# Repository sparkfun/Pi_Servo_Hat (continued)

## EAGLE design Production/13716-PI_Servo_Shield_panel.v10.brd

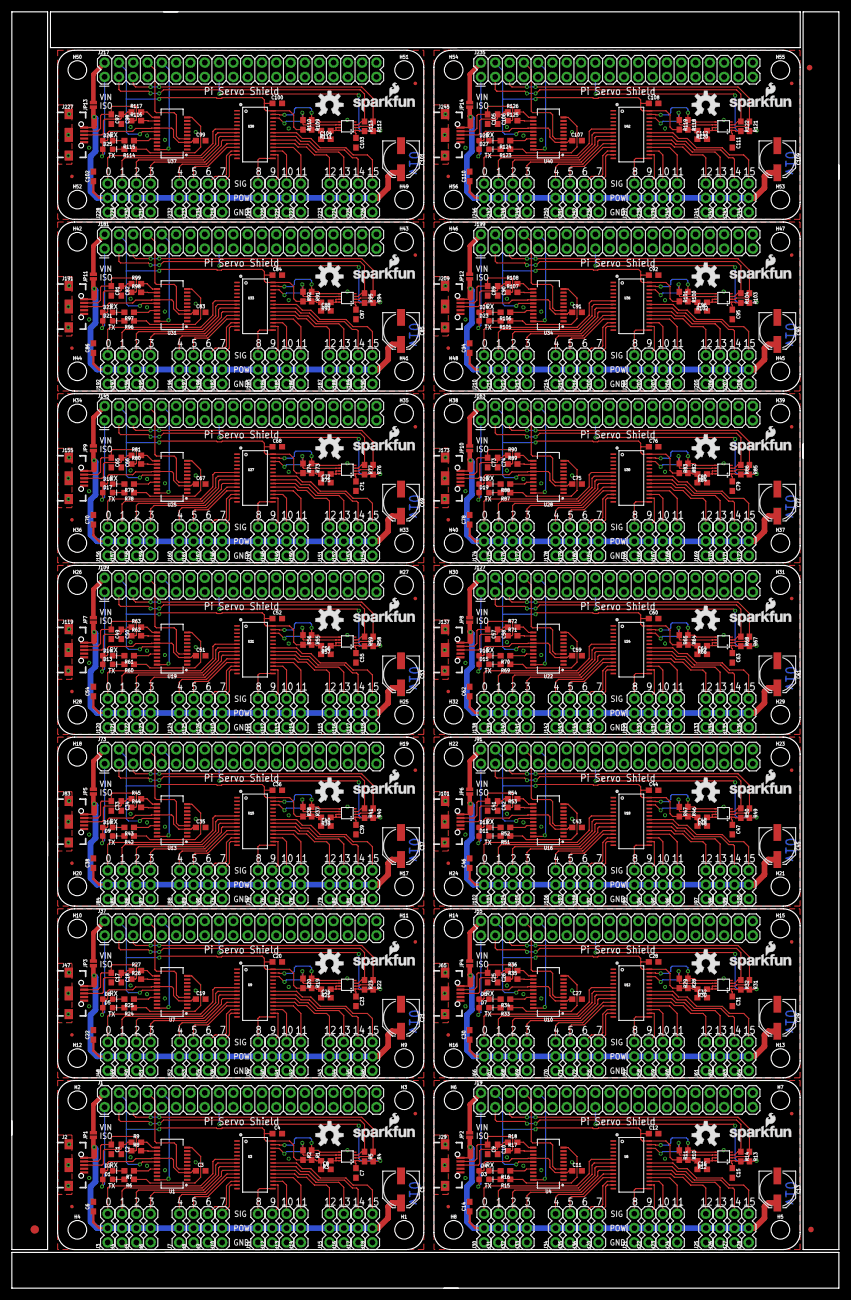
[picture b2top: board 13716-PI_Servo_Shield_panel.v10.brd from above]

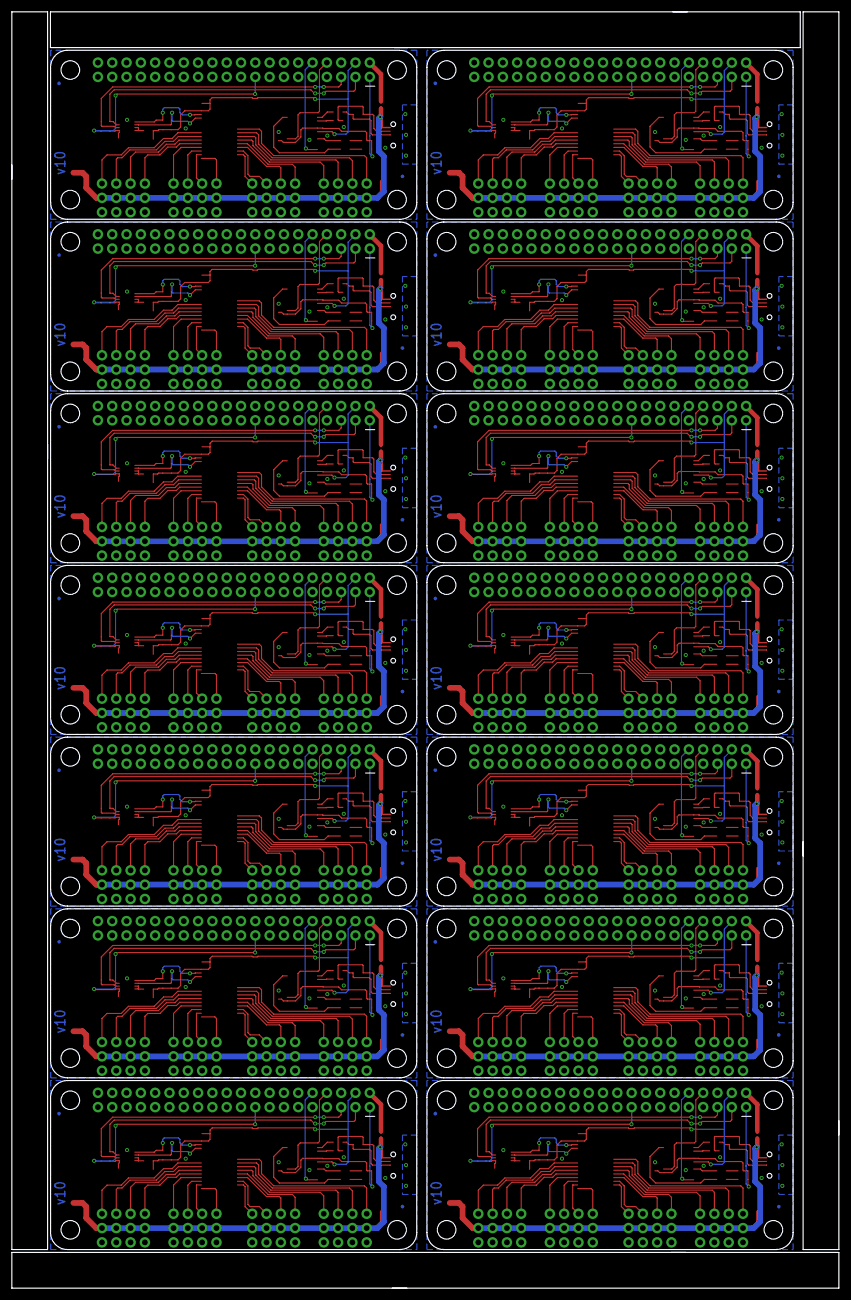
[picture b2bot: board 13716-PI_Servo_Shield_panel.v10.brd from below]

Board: 2 copper layers, 146.8 x 226.6 mm, 717 parts (28 on the bottom side), 532 nets.

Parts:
C1, C2, C9, C10, C17, C18, C25, C26, C33, C34, C41, C42, C49, C50, C57, C58, C65, C66, C73, C74, C81, C82, C89, C90, C97, C98, C105, C106: 47pF; 0603
C3, C4, C6, C7, C8, C11, C12, C14, C15, C16, C19, C20, C22, C23, C24, C27, C28, C30, C31, C32, C35, C36, C38, C39, C40, C43, C44, C46, C47, C48, C51, C52, C54, C55, C56, C59, C60, C62, C63, C64, C67, C68, C70, C71, C72, C75, C76, C78, C79, C80, C83, C84, C86, C87, C88, C91, C92, C94, C95, C96, C99, C100, C102, C103, C104, C107, C108, C110, C111, C112: 0.1uF; 0603
C5, C13, C21, C29, C37, C45, C53, C61, C69, C77, C85, C93, C101, C109: 100uF; PANASONIC_D
D1, D3, D5, D7, D9, D11, D13, D15, D17, D19, D21, D23, D25, D27: GREEN; LED-0603
D2, D4, D6, D8, D10, D12, D14, D16, D18, D20, D22, D24, D26, D28: Yellow; LED-0603
E$1: FIDUCIAL-1.5X3
E$7, E$8: FIDUCIAL-1X2
FD1, FD2, FD3, FD4, FD5, FD6, FD7, FD8, FD9, FD10, FD11, FD12, FD13, FD14, FD15, FD16, FD17, FD18, FD19, FD20, FD21, FD22, FD23, FD24, FD25, FD26, FD27, FD28, FD29, FD30, FD31, FD32, FD33, FD34, FD35, FD36, FD37, FD38, FD39, FD40, FD41, FD42, FD43, FD44, FD45, FD46, FD47, FD48, FD49, FD50, FD51, FD52, FD53, FD54, FD55, FD56: FIDUCIALUFIDUCIAL; FIDUCIAL-MICRO
H1, H2, H3, H4, H5, H6, H7, H8, H9, H10, H11, H12, H13, H14, H15, H16, H17, H18, H19, H20, H21, H22, H23, H24, H25, H26, H27, H28, H29, H30, H31, H32, H33, H34, H35, H36, H37, H38, H39, H40, H41, H42, H43, H44, H45, H46, H47, H48, H49, H50, H51, H52, H53, H54, H55, H56: STAND-OFF
J1, J19, J37, J55, J73, J91, J109, J127, J145, J163, J181, J199, J217, J235: RASPBERRYPI-40-PIN-GPIO_PTH_NO_SHROUD; 2X20
J2, J29, J47, J65, J83, J101, J119, J137, J155, J173, J191, J209, J227, J245: USB-B-MICRO-SMD
J3, J4, J5, J6, J7, J8, J9, J10, J11, J12, J13, J14, J15, J16, J17, J18, J20, J21, J22, J23, J24, J25, J26, J27, J28, J30, J31, J32, J33, J34, J35, J36, J38, J39, J40, J41, J42, J43, J44, J45, J46, J48, J49, J50, J51, J52, J53, J54, J56, J57, J58, J59, J60, J61, J62, J63, J64, J66, J67, J68, J69, J70, J71, J72, J74, J75, J76, J77, J78, J79, J80, J81, J82, J84, J85, J86, J87, J88, J89, J90, J92, J93, J94, J95, J96, J97, J98, J99, J100, J102, J103, J104, J105, J106, J107, J108, J110, J111, J112, J113, J114, J115, J116, J117, J118, J120, J121, J122, J123, J124, J125, J126, J128, J129, J130, J131, J132, J133, J134, J135, J136, J138, J139, J140, J141, J142, J143, J144, J146, J147, J148, J149, J150, J151, J152, J153, J154, J156, J157, J158, J159, J160, J161, J162, J164, J165, J166, J167, J168, J169, J170, J171, J172, J174, J175, J176, J177, J178, J179, J180, J182, J183, J184, J185, J186, J187, J188, J189, J190, J192, J193, J194, J195, J196, J197, J198, J200, J201, J202, J203, J204, J205, J206, J207, J208, J210, J211, J212, J213, J214, J215, J216, J218, J219, J220, J221, J222, J223, J224, J225, J226, J228, J229, J230, J231, J232, J233, J234, J236, J237, J238, J239, J240, J241, J242, J243, J244, J246, J247, J248, J249, J250, J251, J252: 1X03
JP1, JP2, JP3, JP4, JP5, JP6, JP7, JP8, JP9, JP10, JP11, JP12, JP13, JP14: JUMPER-SMT_2_NC_PASTE_NO-SILK; SMT-JUMPER_2_NC_PASTE_NO-SILK
LOGO1, LOGO3, LOGO5, LOGO7, LOGO9, LOGO11, LOGO13, LOGO15, LOGO17, LOGO19, LOGO21, LOGO23, LOGO25, LOGO27: SFE_LOGO_NAME_FLAME.1_INCH; SFE_LOGO_NAME_FLAME_.1
LOGO2, LOGO4, LOGO6, LOGO8, LOGO10, LOGO12, LOGO14, LOGO16, LOGO18, LOGO20, LOGO22, LOGO24, LOGO26, LOGO28: OSHW-LOGOM; OSHW-LOGO-M
R1, R2, R4, R5, R10, R11, R13, R14, R19, R20, R22, R23, R28, R29, R31, R32, R37, R38, R40, R41, R46, R47, R49, R50, R55, R56, R58, R59, R64, R65, R67, R68, R73, R74, R76, R77, R82, R83, R85, R86, R91, R92, R94, R95, R100, R101, R103, R104, R109, R110, R112, R113, R118, R119, R121, R122: 10k; 0603
R3, R12, R21, R30, R39, R48, R57, R66, R75, R84, R93, R102, R111, R120: 200k; 0603
R6, R7, R15, R16, R24, R25, R33, R34, R42, R43, R51, R52, R60, R61, R69, R70, R78, R79, R87, R88, R96, R97, R105, R106, R114, R115, R123, R124: 1k; 0603
R8, R9, R17, R18, R26, R27, R35, R36, R44, R45, R53, R54, R62, R63, R71, R72, R80, R81, R89, R90, R98, R99, R107, R108, R116, R117, R125, R126: 27; 0603
U1, U4, U7, U10, U13, U16, U19, U22, U25, U28, U31, U34, U37, U40: FT231XS; SSOP20_L
U2, U5, U8, U11, U14, U17, U20, U23, U26, U29, U32, U35, U38, U41: PCA9306; PSOP-8
U3, U6, U9, U12, U15, U18, U21, U24, U27, U30, U33, U36, U39, U42: PCA9685; TSSOP-28_4MM

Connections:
3.3VA: C3.1, D1.A, D2.A, J1.1, U1.3, U1.14
3.3VA1: C11.1, D3.A, D4.A, J19.1, U4.3, U4.14
3.3VA2: C19.1, D5.A, D6.A, J37.1, U7.3, U7.14
3.3VA3: C27.1, D7.A, D8.A, J55.1, U10.3, U10.14
3.3VA4: C35.1, D9.A, D10.A, J73.1, U13.3, U13.14
3.3VA5: C43.1, D11.A, D12.A, J91.1, U16.3, U16.14
3.3VA6: C51.1, D13.A, D14.A, J109.1, U19.3, U19.14
3.3VA7: C59.1, D15.A, D16.A, J127.1, U22.3, U22.14
3.3VA8: C67.1, D17.A, D18.A, J145.1, U25.3, U25.14
3.3VA9: C75.1, D19.A, D20.A, J163.1, U28.3, U28.14
3.3VA10: C83.1, D21.A, D22.A, J181.1, U31.3, U31.14
3.3VA11: C91.1, D23.A, D24.A, J199.1, U34.3, U34.14
3.3VA12: C99.1, D25.A, D26.A, J217.1, U37.3, U37.14
3.3VA13: C107.1, D27.A, D28.A, J235.1, U40.3, U40.14
3.3VB: C7.1, J1.17, R4.2, R5.2, U2.1
3.3VB1: C15.1, J19.17, R13.2, R14.2, U5.1
3.3VB2: C23.1, J37.17, R22.2, R23.2, U8.1
3.3VB3: C31.1, J55.17, R31.2, R32.2, U11.1
3.3VB4: C39.1, J73.17, R40.2, R41.2, U14.1
3.3VB5: C47.1, J91.17, R49.2, R50.2, U17.1
3.3VB6: C55.1, J109.17, R58.2, R59.2, U20.1
3.3VB7: C63.1, J127.17, R67.2, R68.2, U23.1
3.3VB8: C71.1, J145.17, R76.2, R77.2, U26.1
3.3VB9: C79.1, J163.17, R85.2, R86.2, U29.1
3.3VB10: C87.1, J181.17, R94.2, R95.2, U32.1
3.3VB11: C95.1, J199.17, R103.2, R104.2, U35.1
3.3VB12: C103.1, J217.17, R112.2, R113.2, U38.1
3.3VB13: C111.1, J235.17, R121.2, R122.2, U41.1
5VA: J1.2, JP1.2
5VA1: J19.2, JP2.2
5VA2: J37.2, JP3.2
5VA3: J55.2, JP4.2
5VA4: J73.2, JP5.2
5VA5: J91.2, JP6.2
5VA6: J109.2, JP7.2
5VA7: J127.2, JP8.2
5VA8: J145.2, JP9.2
5VA9: J163.2, JP10.2
5VA10: J181.2, JP11.2
5VA11: J199.2, JP12.2
5VA12: J217.2, JP13.2
5VA13: J235.2, JP14.2
5VB: C4.1, C8.1, J1.4, R1.2, R2.2, R3.2, U1.15, U3.28
5VB1: C12.1, C16.1, J19.4, R10.2, R11.2, R12.2, U4.15, U6.28
5VB2: C20.1, C24.1, J37.4, R19.2, R20.2, R21.2, U7.15, U9.28
5VB3: C28.1, C32.1, J55.4, R28.2, R29.2, R30.2, U10.15, U12.28
5VB4: C36.1, C40.1, J73.4, R37.2, R38.2, R39.2, U13.15, U15.28
5VB5: C44.1, C48.1, J91.4, R46.2, R47.2, R48.2, U16.15, U18.28
5VB6: C52.1, C56.1, J109.4, R55.2, R56.2, R57.2, U19.15, U21.28
5VB7: C60.1, C64.1, J127.4, R64.2, R65.2, R66.2, U22.15, U24.28
5VB8: C68.1, C72.1, J145.4, R73.2, R74.2, R75.2, U25.15, U27.28
5VB9: C76.1, C80.1, J163.4, R82.2, R83.2, R84.2, U28.15, U30.28
5VB10: C84.1, C88.1, J181.4, R91.2, R92.2, R93.2, U31.15, U33.28
5VB11: C92.1, C96.1, J199.4, R100.2, R101.2, R102.2, U34.15, U36.28
5VB12: C100.1, C104.1, J217.4, R109.2, R110.2, R111.2, U37.15, U39.28
5VB13: C108.1, C112.1, J235.4, R118.2, R119.2, R120.2, U40.15, U42.28
CH0: J3.3, U3.6
CH1: J4.3, U3.7
CH2: J5.3, U3.8
CH3: J6.3, U3.9
CH4: J7.3, U3.10
CH5: J8.3, U3.11
CH6: J9.3, U3.12
CH7: J10.3, U3.13
CH8: J11.3, U3.15
CH9: J12.3, U3.16
CH10: J13.3, U3.17
CH11: J14.3, U3.18
CH12: J15.3, U3.19
CH13: J16.3, U3.20
CH14: J17.3, U3.21
CH15: J18.3, U3.22
CH16: J28.3, U6.22
CH17: J27.3, U6.21
CH18: J26.3, U6.20
CH19: J25.3, U6.19
CH20: J24.3, U6.18
CH21: J23.3, U6.17
CH22: J22.3, U6.16
CH23: J21.3, U6.15
CH24: J36.3, U6.12
CH25: J35.3, U6.11
CH26: J34.3, U6.10
CH27: J33.3, U6.9
CH28: J32.3, U6.8
CH29: J31.3, U6.7
CH30: J30.3, U6.6
CH31: J20.3, U6.13
CH32: J46.3, U9.22
CH33: J45.3, U9.21
CH34: J44.3, U9.20
CH35: J43.3, U9.19
CH36: J42.3, U9.18
CH37: J41.3, U9.17
CH38: J40.3, U9.16
CH39: J39.3, U9.15
CH40: J54.3, U9.12
CH41: J53.3, U9.11
CH42: J52.3, U9.10
CH43: J51.3, U9.9
CH44: J50.3, U9.8
CH45: J49.3, U9.7
CH46: J48.3, U9.6
CH47: J38.3, U9.13
CH48: J64.3, U12.22
CH49: J63.3, U12.21
CH50: J62.3, U12.20
CH51: J61.3, U12.19
CH52: J60.3, U12.18
CH53: J59.3, U12.17
CH54: J58.3, U12.16
CH55: J57.3, U12.15
CH56: J72.3, U12.12
CH57: J71.3, U12.11
CH58: J70.3, U12.10
CH59: J69.3, U12.9
CH60: J68.3, U12.8
CH61: J67.3, U12.7
CH62: J66.3, U12.6
CH63: J56.3, U12.13
CH64: J82.3, U15.22
CH65: J81.3, U15.21
CH66: J80.3, U15.20
CH67: J79.3, U15.19
CH68: J78.3, U15.18
CH69: J77.3, U15.17
CH70: J76.3, U15.16
CH71: J75.3, U15.15
CH72: J90.3, U15.12
CH73: J89.3, U15.11
CH74: J88.3, U15.10
CH75: J87.3, U15.9
CH76: J86.3, U15.8
CH77: J85.3, U15.7
CH78: J84.3, U15.6
CH79: J74.3, U15.13
CH80: J100.3, U18.22
CH81: J99.3, U18.21
CH82: J98.3, U18.20
CH83: J97.3, U18.19
CH84: J96.3, U18.18
CH85: J95.3, U18.17
CH86: J94.3, U18.16
CH87: J93.3, U18.15
CH88: J108.3, U18.12
CH89: J107.3, U18.11
CH90: J106.3, U18.10
CH91: J105.3, U18.9
CH92: J104.3, U18.8
CH93: J103.3, U18.7
CH94: J102.3, U18.6
CH95: J92.3, U18.13
CH96: J118.3, U21.22
CH97: J117.3, U21.21
CH98: J116.3, U21.20
CH99: J115.3, U21.19
CH100: J114.3, U21.18
CH101: J113.3, U21.17
CH102: J112.3, U21.16
CH103: J111.3, U21.15
CH104: J126.3, U21.12
CH105: J125.3, U21.11
CH106: J124.3, U21.10
CH107: J123.3, U21.9
CH108: J122.3, U21.8
CH109: J121.3, U21.7
CH110: J120.3, U21.6
CH111: J110.3, U21.13
CH112: J136.3, U24.22
CH113: J135.3, U24.21
CH114: J134.3, U24.20
CH115: J133.3, U24.19
CH116: J132.3, U24.18
CH117: J131.3, U24.17
CH118: J130.3, U24.16
CH119: J129.3, U24.15
CH120: J144.3, U24.12
CH121: J143.3, U24.11
CH122: J142.3, U24.10
CH123: J141.3, U24.9
CH124: J140.3, U24.8
CH125: J139.3, U24.7
CH126: J138.3, U24.6
CH127: J128.3, U24.13
CH128: J154.3, U27.22
CH129: J153.3, U27.21
CH130: J152.3, U27.20
CH131: J151.3, U27.19
CH132: J150.3, U27.18
CH133: J149.3, U27.17
CH134: J148.3, U27.16
CH135: J147.3, U27.15
CH136: J162.3, U27.12
CH137: J161.3, U27.11
CH138: J160.3, U27.10
CH139: J159.3, U27.9
CH140: J158.3, U27.8
CH141: J157.3, U27.7
CH142: J156.3, U27.6
CH143: J146.3, U27.13
CH144: J172.3, U30.22
CH145: J171.3, U30.21
CH146: J170.3, U30.20
CH147: J169.3, U30.19
CH148: J168.3, U30.18
CH149: J167.3, U30.17
CH150: J166.3, U30.16
CH151: J165.3, U30.15
CH152: J180.3, U30.12
CH153: J179.3, U30.11
CH154: J178.3, U30.10
CH155: J177.3, U30.9
CH156: J176.3, U30.8
CH157: J175.3, U30.7
CH158: J174.3, U30.6
CH159: J164.3, U30.13
CH160: J190.3, U33.22
CH161: J189.3, U33.21
CH162: J188.3, U33.20
CH163: J187.3, U33.19
CH164: J186.3, U33.18
CH165: J185.3, U33.17
CH166: J184.3, U33.16
CH167: J183.3, U33.15
CH168: J198.3, U33.12
CH169: J197.3, U33.11
CH170: J196.3, U33.10
CH171: J195.3, U33.9
CH172: J194.3, U33.8
CH173: J193.3, U33.7
CH174: J192.3, U33.6
CH175: J182.3, U33.13
CH176: J208.3, U36.22
CH177: J207.3, U36.21
CH178: J206.3, U36.20
CH179: J205.3, U36.19
CH180: J204.3, U36.18
CH181: J203.3, U36.17
CH182: J202.3, U36.16
CH183: J201.3, U36.15
CH184: J216.3, U36.12
CH185: J215.3, U36.11
CH186: J214.3, U36.10
CH187: J213.3, U36.9
CH188: J212.3, U36.8
CH189: J211.3, U36.7
CH190: J210.3, U36.6
CH191: J200.3, U36.13
CH192: J226.3, U39.22
CH193: J225.3, U39.21
CH194: J224.3, U39.20
CH195: J223.3, U39.19
CH196: J222.3, U39.18
CH197: J221.3, U39.17
CH198: J220.3, U39.16
CH199: J219.3, U39.15
CH200: J234.3, U39.12
CH201: J233.3, U39.11
CH202: J232.3, U39.10
CH203: J231.3, U39.9
CH204: J230.3, U39.8
CH205: J229.3, U39.7
CH206: J228.3, U39.6
CH207: J218.3, U39.13
CH208: J244.3, U42.22
CH209: J243.3, U42.21
CH210: J242.3, U42.20
CH211: J241.3, U42.19
CH212: J240.3, U42.18
CH213: J239.3, U42.17
CH214: J238.3, U42.16
CH215: J237.3, U42.15
CH216: J252.3, U42.12
CH217: J251.3, U42.11
CH218: J250.3, U42.10
CH219: J249.3, U42.9
CH220: J248.3, U42.8
CH221: J247.3, U42.7
CH222: J246.3, U42.6
CH223: J236.3, U42.13
GND: C1.2, C2.2, C3.2, C4.2, C5.-, C6.2, C7.2, C8.2, J1.6, J1.9, J1.14, J1.20, J1.25, J1.30, J1.34, J1.39, J2.GND, J3.1, J4.1, J5.1, J6.1, J7.1, J8.1, J9.1, J10.1, J11.1, J12.1, J13.1, J14.1, J15.1, J16.1, J17.1, J18.1, U1.6, U1.16, U2.4, U3.14, U3.23, U3.25
GND1: C9.2, C10.2, C11.2, C12.2, C13.-, C14.2, C15.2, C16.2, J19.6, J19.9, J19.14, J19.20, J19.25, J19.30, J19.34, J19.39, J20.1, J21.1, J22.1, J23.1, J24.1, J25.1, J26.1, J27.1, J28.1, J29.GND, J30.1, J31.1, J32.1, J33.1, J34.1, J35.1, J36.1, U4.6, U4.16, U5.4, U6.14, U6.23, U6.25
GND2: C17.2, C18.2, C19.2, C20.2, C21.-, C22.2, C23.2, C24.2, J37.6, J37.9, J37.14, J37.20, J37.25, J37.30, J37.34, J37.39, J38.1, J39.1, J40.1, J41.1, J42.1, J43.1, J44.1, J45.1, J46.1, J47.GND, J48.1, J49.1, J50.1, J51.1, J52.1, J53.1, J54.1, U7.6, U7.16, U8.4, U9.14, U9.23, U9.25
GND3: C25.2, C26.2, C27.2, C28.2, C29.-, C30.2, C31.2, C32.2, J55.6, J55.9, J55.14, J55.20, J55.25, J55.30, J55.34, J55.39, J56.1, J57.1, J58.1, J59.1, J60.1, J61.1, J62.1, J63.1, J64.1, J65.GND, J66.1, J67.1, J68.1, J69.1, J70.1, J71.1, J72.1, U10.6, U10.16, U11.4, U12.14, U12.23, U12.25
GND4: C33.2, C34.2, C35.2, C36.2, C37.-, C38.2, C39.2, C40.2, J73.6, J73.9, J73.14, J73.20, J73.25, J73.30, J73.34, J73.39, J74.1, J75.1, J76.1, J77.1, J78.1, J79.1, J80.1, J81.1, J82.1, J83.GND, J84.1, J85.1, J86.1, J87.1, J88.1, J89.1, J90.1, U13.6, U13.16, U14.4, U15.14, U15.23, U15.25
GND5: C41.2, C42.2, C43.2, C44.2, C45.-, C46.2, C47.2, C48.2, J91.6, J91.9, J91.14, J91.20, J91.25, J91.30, J91.34, J91.39, J92.1, J93.1, J94.1, J95.1, J96.1, J97.1, J98.1, J99.1, J100.1, J101.GND, J102.1, J103.1, J104.1, J105.1, J106.1, J107.1, J108.1, U16.6, U16.16, U17.4, U18.14, U18.23, U18.25
GND6: C49.2, C50.2, C51.2, C52.2, C53.-, C54.2, C55.2, C56.2, J109.6, J109.9, J109.14, J109.20, J109.25, J109.30, J109.34, J109.39, J110.1, J111.1, J112.1, J113.1, J114.1, J115.1, J116.1, J117.1, J118.1, J119.GND, J120.1, J121.1, J122.1, J123.1, J124.1, J125.1, J126.1, U19.6, U19.16, U20.4, U21.14, U21.23, U21.25
GND7: C57.2, C58.2, C59.2, C60.2, C61.-, C62.2, C63.2, C64.2, J127.6, J127.9, J127.14, J127.20, J127.25, J127.30, J127.34, J127.39, J128.1, J129.1, J130.1, J131.1, J132.1, J133.1, J134.1, J135.1, J136.1, J137.GND, J138.1, J139.1, J140.1, J141.1, J142.1, J143.1, J144.1, U22.6, U22.16, U23.4, U24.14, U24.23, U24.25
GND8: C65.2, C66.2, C67.2, C68.2, C69.-, C70.2, C71.2, C72.2, J145.6, J145.9, J145.14, J145.20, J145.25, J145.30, J145.34, J145.39, J146.1, J147.1, J148.1, J149.1, J150.1, J151.1, J152.1, J153.1, J154.1, J155.GND, J156.1, J157.1, J158.1, J159.1, J160.1, J161.1, J162.1, U25.6, U25.16, U26.4, U27.14, U27.23, U27.25
GND9: C73.2, C74.2, C75.2, C76.2, C77.-, C78.2, C79.2, C80.2, J163.6, J163.9, J163.14, J163.20, J163.25, J163.30, J163.34, J163.39, J164.1, J165.1, J166.1, J167.1, J168.1, J169.1, J170.1, J171.1, J172.1, J173.GND, J174.1, J175.1, J176.1, J177.1, J178.1, J179.1, J180.1, U28.6, U28.16, U29.4, U30.14, U30.23, U30.25
GND10: C81.2, C82.2, C83.2, C84.2, C85.-, C86.2, C87.2, C88.2, J181.6, J181.9, J181.14, J181.20, J181.25, J181.30, J181.34, J181.39, J182.1, J183.1, J184.1, J185.1, J186.1, J187.1, J188.1, J189.1, J190.1, J191.GND, J192.1, J193.1, J194.1, J195.1, J196.1, J197.1, J198.1, U31.6, U31.16, U32.4, U33.14, U33.23, U33.25
GND11: C89.2, C90.2, C91.2, C92.2, C93.-, C94.2, C95.2, C96.2, J199.6, J199.9, J199.14, J199.20, J199.25, J199.30, J199.34, J199.39, J200.1, J201.1, J202.1, J203.1, J204.1, J205.1, J206.1, J207.1, J208.1, J209.GND, J210.1, J211.1, J212.1, J213.1, J214.1, J215.1, J216.1, U34.6, U34.16, U35.4, U36.14, U36.23, U36.25
GND12: C97.2, C98.2, C99.2, C100.2, C101.-, C102.2, C103.2, C104.2, J217.6, J217.9, J217.14, J217.20, J217.25, J217.30, J217.34, J217.39, J218.1, J219.1, J220.1, J221.1, J222.1, J223.1, J224.1, J225.1, J226.1, J227.GND, J228.1, J229.1, J230.1, J231.1, J232.1, J233.1, J234.1, U37.6, U37.16, U38.4, U39.14, U39.23, U39.25
GND13: C105.2, C106.2, C107.2, C108.2, C109.-, C110.2, C111.2, C112.2, J235.6, J235.9, J235.14, J235.20, J235.25, J235.30, J235.34, J235.39, J236.1, J237.1, J238.1, J239.1, J240.1, J241.1, J242.1, J243.1, J244.1, J245.GND, J246.1, J247.1, J248.1, J249.1, J250.1, J251.1, J252.1, U40.6, U40.16, U41.4, U42.14, U42.23, U42.25
LV_SCL: J1.5, R4.1, U2.2
LV_SCL1: J19.5, R13.1, U5.2
LV_SCL2: J37.5, R22.1, U8.2
LV_SCL3: J55.5, R31.1, U11.2
LV_SCL4: J73.5, R40.1, U14.2
LV_SCL5: J91.5, R49.1, U17.2
LV_SCL6: J109.5, R58.1, U20.2
LV_SCL7: J127.5, R67.1, U23.2
LV_SCL8: J145.5, R76.1, U26.2
LV_SCL9: J163.5, R85.1, U29.2
LV_SCL10: J181.5, R94.1, U32.2
LV_SCL11: J199.5, R103.1, U35.2
LV_SCL12: J217.5, R112.1, U38.2
LV_SCL13: J235.5, R121.1, U41.2
LV_SDA: J1.3, R5.1, U2.3
LV_SDA1: J19.3, R14.1, U5.3
LV_SDA2: J37.3, R23.1, U8.3
LV_SDA3: J55.3, R32.1, U11.3
LV_SDA4: J73.3, R41.1, U14.3
LV_SDA5: J91.3, R50.1, U17.3
LV_SDA6: J109.3, R59.1, U20.3
LV_SDA7: J127.3, R68.1, U23.3
LV_SDA8: J145.3, R77.1, U26.3
LV_SDA9: J163.3, R86.1, U29.3
LV_SDA10: J181.3, R95.1, U32.3
LV_SDA11: J199.3, R104.1, U35.3
LV_SDA12: J217.3, R113.1, U38.3
LV_SDA13: J235.3, R122.1, U41.3
unnamed: R3.1, U2.7, U2.8
unnamed: R8.2, U1.12
unnamed: R2.1, U2.6, U3.26
unnamed: R1.1, U2.5, U3.27
unnamed: D2.C, R7.2
unnamed: D1.C, R6.2
unnamed: R7.1, U1.17
unnamed: R6.1, U1.10
unnamed: R9.2, U1.11
unnamed: C2.1, J2.D+, R9.1
unnamed: C1.1, J2.D-, R8.1
unnamed: R12.1, U5.7, U5.8
unnamed: R11.1, U5.6, U6.26
unnamed: R10.1, U5.5, U6.27
unnamed: D4.C, R16.2
unnamed: D3.C, R15.2
unnamed: R16.1, U4.17
unnamed: R15.1, U4.10
unnamed: R17.2, U4.12
unnamed: R18.2, U4.11
unnamed: C10.1, J29.D+, R18.1
unnamed: C9.1, J29.D-, R17.1
unnamed: R21.1, U8.7, U8.8
unnamed: R20.1, U8.6, U9.26
unnamed: R19.1, U8.5, U9.27
unnamed: D6.C, R25.2
unnamed: D5.C, R24.2
unnamed: R25.1, U7.17
unnamed: R24.1, U7.10
unnamed: R26.2, U7.12
unnamed: R27.2, U7.11
unnamed: C18.1, J47.D+, R27.1
unnamed: C17.1, J47.D-, R26.1
unnamed: R30.1, U11.7, U11.8
unnamed: R29.1, U11.6, U12.26
unnamed: R28.1, U11.5, U12.27
unnamed: D8.C, R34.2
unnamed: D7.C, R33.2
unnamed: R34.1, U10.17
unnamed: R33.1, U10.10
unnamed: R35.2, U10.12
unnamed: R36.2, U10.11
unnamed: C26.1, J65.D+, R36.1
unnamed: C25.1, J65.D-, R35.1
unnamed: R39.1, U14.7, U14.8
unnamed: R38.1, U14.6, U15.26
unnamed: R37.1, U14.5, U15.27
unnamed: D10.C, R43.2
unnamed: D9.C, R42.2
unnamed: R43.1, U13.17
unnamed: R42.1, U13.10
unnamed: R44.2, U13.12
unnamed: R45.2, U13.11
unnamed: C34.1, J83.D+, R45.1
unnamed: C33.1, J83.D-, R44.1
unnamed: R48.1, U17.7, U17.8
unnamed: R47.1, U17.6, U18.26
unnamed: R46.1, U17.5, U18.27
unnamed: D12.C, R52.2
unnamed: D11.C, R51.2
unnamed: R52.1, U16.17
unnamed: R51.1, U16.10
unnamed: R53.2, U16.12
unnamed: R54.2, U16.11
unnamed: C42.1, J101.D+, R54.1
unnamed: C41.1, J101.D-, R53.1
unnamed: R57.1, U20.7, U20.8
unnamed: R56.1, U20.6, U21.26
unnamed: R55.1, U20.5, U21.27
unnamed: D14.C, R61.2
unnamed: D13.C, R60.2
unnamed: R61.1, U19.17
unnamed: R60.1, U19.10
unnamed: R62.2, U19.12
unnamed: R63.2, U19.11
unnamed: C50.1, J119.D+, R63.1
unnamed: C49.1, J119.D-, R62.1
unnamed: R66.1, U23.7, U23.8
unnamed: R65.1, U23.6, U24.26
unnamed: R64.1, U23.5, U24.27
unnamed: D16.C, R70.2
unnamed: D15.C, R69.2
unnamed: R70.1, U22.17
unnamed: R69.1, U22.10
unnamed: R71.2, U22.12
unnamed: R72.2, U22.11
unnamed: C58.1, J137.D+, R72.1
unnamed: C57.1, J137.D-, R71.1
unnamed: R75.1, U26.7, U26.8
unnamed: R74.1, U26.6, U27.26
unnamed: R73.1, U26.5, U27.27
unnamed: D18.C, R79.2
unnamed: D17.C, R78.2
unnamed: R79.1, U25.17
unnamed: R78.1, U25.10
unnamed: R80.2, U25.12
unnamed: R81.2, U25.11
unnamed: C66.1, J155.D+, R81.1
unnamed: C65.1, J155.D-, R80.1
unnamed: R84.1, U29.7, U29.8
unnamed: R83.1, U29.6, U30.26
unnamed: R82.1, U29.5, U30.27
unnamed: D20.C, R88.2
unnamed: D19.C, R87.2
unnamed: R88.1, U28.17
unnamed: R87.1, U28.10
unnamed: R89.2, U28.12
unnamed: R90.2, U28.11
unnamed: C74.1, J173.D+, R90.1
unnamed: C73.1, J173.D-, R89.1
unnamed: R93.1, U32.7, U32.8
unnamed: R92.1, U32.6, U33.26
unnamed: R91.1, U32.5, U33.27
unnamed: D22.C, R97.2
unnamed: D21.C, R96.2
unnamed: R97.1, U31.17
unnamed: R96.1, U31.10
unnamed: R98.2, U31.12
unnamed: R99.2, U31.11
unnamed: C82.1, J191.D+, R99.1
unnamed: C81.1, J191.D-, R98.1
unnamed: R102.1, U35.7, U35.8
unnamed: R101.1, U35.6, U36.26
unnamed: R100.1, U35.5, U36.27
unnamed: D24.C, R106.2
unnamed: D23.C, R105.2
unnamed: R106.1, U34.17
unnamed: R105.1, U34.10
unnamed: R107.2, U34.12
unnamed: R108.2, U34.11
unnamed: C90.1, J209.D+, R108.1
unnamed: C89.1, J209.D-, R107.1
unnamed: R111.1, U38.7, U38.8
unnamed: R110.1, U38.6, U39.26
unnamed: R109.1, U38.5, U39.27
unnamed: D26.C, R115.2
unnamed: D25.C, R114.2
unnamed: R115.1, U37.17
unnamed: R114.1, U37.10
unnamed: R116.2, U37.12
unnamed: R117.2, U37.11
unnamed: C98.1, J227.D+, R117.1
unnamed: C97.1, J227.D-, R116.1
unnamed: R120.1, U41.7, U41.8
unnamed: R119.1, U41.6, U42.26
unnamed: R118.1, U41.5, U42.27
unnamed: D28.C, R124.2
unnamed: D27.C, R123.2
unnamed: R124.1, U40.17
unnamed: R123.1, U40.10
unnamed: R125.2, U40.12
unnamed: R126.2, U40.11
unnamed: C106.1, J245.D+, R126.1
unnamed: C105.1, J245.D-, R125.1
RXD: J1.8, U1.4
RXD1: J19.8, U4.4
RXD2: J37.8, U7.4
RXD3: J55.8, U10.4
RXD4: J73.8, U13.4
RXD5: J91.8, U16.4
RXD6: J109.8, U19.4
RXD7: J127.8, U22.4
RXD8: J145.8, U25.4
RXD9: J163.8, U28.4
RXD10: J181.8, U31.4
RXD11: J199.8, U34.4
RXD12: J217.8, U37.4
RXD13: J235.8, U40.4
SHIELD: J2.SHIELD1, J2.SHIELD2, J2.SHIELD3
SHIELD1: J29.SHIELD1, J29.SHIELD2, J29.SHIELD3
SHIELD2: J47.SHIELD1, J47.SHIELD2, J47.SHIELD3
SHIELD3: J65.SHIELD1, J65.SHIELD2, J65.SHIELD3
SHIELD4: J83.SHIELD1, J83.SHIELD2, J83.SHIELD3
SHIELD5: J101.SHIELD1, J101.SHIELD2, J101.SHIELD3
SHIELD6: J119.SHIELD1, J119.SHIELD2, J119.SHIELD3
SHIELD7: J137.SHIELD1, J137.SHIELD2, J137.SHIELD3
SHIELD8: J155.SHIELD1, J155.SHIELD2, J155.SHIELD3
SHIELD9: J173.SHIELD1, J173.SHIELD2, J173.SHIELD3
SHIELD10: J191.SHIELD1, J191.SHIELD2, J191.SHIELD3
SHIELD11: J209.SHIELD1, J209.SHIELD2, J209.SHIELD3
SHIELD12: J227.SHIELD1, J227.SHIELD2, J227.SHIELD3
SHIELD13: J245.SHIELD1, J245.SHIELD2, J245.SHIELD3
TXD: J1.10, U1.20
TXD1: J19.10, U4.20
TXD2: J37.10, U7.20
TXD3: J55.10, U10.20
TXD4: J73.10, U13.20
TXD5: J91.10, U16.20
TXD6: J109.10, U19.20
TXD7: J127.10, U22.20
TXD8: J145.10, U25.20
TXD9: J163.10, U28.20
TXD10: J181.10, U31.20
TXD11: J199.10, U34.20
TXD12: J217.10, U37.20
TXD13: J235.10, U40.20
VIN: C5.+, C6.1, J2.VBUS, J3.2, J4.2, J5.2, J6.2, J7.2, J8.2, J9.2, J10.2, J11.2, J12.2, J13.2, J14.2, J15.2, J16.2, J17.2, J18.2, JP1.1
VIN1: C13.+, C14.1, J20.2, J21.2, J22.2, J23.2, J24.2, J25.2, J26.2, J27.2, J28.2, J29.VBUS, J30.2, J31.2, J32.2, J33.2, J34.2, J35.2, J36.2, JP2.1
VIN2: C21.+, C22.1, J38.2, J39.2, J40.2, J41.2, J42.2, J43.2, J44.2, J45.2, J46.2, J47.VBUS, J48.2, J49.2, J50.2, J51.2, J52.2, J53.2, J54.2, JP3.1
VIN3: C29.+, C30.1, J56.2, J57.2, J58.2, J59.2, J60.2, J61.2, J62.2, J63.2, J64.2, J65.VBUS, J66.2, J67.2, J68.2, J69.2, J70.2, J71.2, J72.2, JP4.1
VIN4: C37.+, C38.1, J74.2, J75.2, J76.2, J77.2, J78.2, J79.2, J80.2, J81.2, J82.2, J83.VBUS, J84.2, J85.2, J86.2, J87.2, J88.2, J89.2, J90.2, JP5.1
VIN5: C45.+, C46.1, J92.2, J93.2, J94.2, J95.2, J96.2, J97.2, J98.2, J99.2, J100.2, J101.VBUS, J102.2, J103.2, J104.2, J105.2, J106.2, J107.2, J108.2, JP6.1
VIN6: C53.+, C54.1, J110.2, J111.2, J112.2, J113.2, J114.2, J115.2, J116.2, J117.2, J118.2, J119.VBUS, J120.2, J121.2, J122.2, J123.2, J124.2, J125.2, J126.2, JP7.1
VIN7: C61.+, C62.1, J128.2, J129.2, J130.2, J131.2, J132.2, J133.2, J134.2, J135.2, J136.2, J137.VBUS, J138.2, J139.2, J140.2, J141.2, J142.2, J143.2, J144.2, JP8.1
VIN8: C69.+, C70.1, J146.2, J147.2, J148.2, J149.2, J150.2, J151.2, J152.2, J153.2, J154.2, J155.VBUS, J156.2, J157.2, J158.2, J159.2, J160.2, J161.2, J162.2, JP9.1
VIN9: C77.+, C78.1, J164.2, J165.2, J166.2, J167.2, J168.2, J169.2, J170.2, J171.2, J172.2, J173.VBUS, J174.2, J175.2, J176.2, J177.2, J178.2, J179.2, J180.2, JP10.1
VIN10: C85.+, C86.1, J182.2, J183.2, J184.2, J185.2, J186.2, J187.2, J188.2, J189.2, J190.2, J191.VBUS, J192.2, J193.2, J194.2, J195.2, J196.2, J197.2, J198.2, JP11.1
VIN11: C93.+, C94.1, J200.2, J201.2, J202.2, J203.2, J204.2, J205.2, J206.2, J207.2, J208.2, J209.VBUS, J210.2, J211.2, J212.2, J213.2, J214.2, J215.2, J216.2, JP12.1
VIN12: C101.+, C102.1, J218.2, J219.2, J220.2, J221.2, J222.2, J223.2, J224.2, J225.2, J226.2, J227.VBUS, J228.2, J229.2, J230.2, J231.2, J232.2, J233.2, J234.2, JP13.1
VIN13: C109.+, C110.1, J236.2, J237.2, J238.2, J239.2, J240.2, J241.2, J242.2, J243.2, J244.2, J245.VBUS, J246.2, J247.2, J248.2, J249.2, J250.2, J251.2, J252.2, JP14.1

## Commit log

2017-05-17 Changes based on talk with Adam
2017-05-23 Changes from review feedback
2017-05-24 Addressed errors from double check
2017-06-15 Change version number
2017-06-21 Change to v10
2017-06-26 panel
2017-09-06 Add README.md
2017-09-07 Add examples
2017-09-07 Add cpp example
2017-09-11 Change shield to hat in readme
2018-02-15 Fix incorrect code
    fixed the address to 0x40 rather than 0x20, to match the actual address and the pan tilt code. Also changed time.sleep to 2 seconds, rather than 2000 (python's time.sleep is in seconds, not milisecon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
2018-08-02 Rename example.cpp to example_original.cpp
2018-08-02 Rename example.py to example_original.py
2018-08-02 Rename example_original.cpp to example_200Hz.cpp
2018-08-02 Rename example_original.py to example_200Hz.py
2018-08-02 Rename servohat_200.py to servohat_200Hz_tuned.py
2018-08-02 Rename servohat_50.py to servohat_50Hz_tuned.py
2018-08-02 Rename example_200Hz.cpp to example_200Hz_original.cpp
2018-08-02 Rename example_200Hz.py to example_200Hz_original.py
2019-03-22 v20 hardwaer 99% done - still needs buzzard migration
2019-03-25 Buzzard migration complete
    Also nudged some stuff to avoid silk on vias and to make room for a few labels.
2019-03-25 locking fp on serial header, sch cleanup
2019-03-25 adjusted I2C pullup and label
    modified sch note for bypass fuse jumper
2019-03-26 post proto-design-review
    SCH cleanup:
    -3.3VA and 3.3VB combined into a single net and changed to arrow power symbol
    -5VA and 5VB combined into a single net and changed to arrow power symbol
    -added note about serial connector mating with sphero RVR
    -version to v11, will jump to v20 when going to reds
    BRD:
2019-03-27 Updated name silk label to include "V2"
2019-03-27 post checklist changes - silk and testpoints
    -silk outlines up to 8 mil on a few.
    -testpoints
    -RX/TX LED colors corrected
    -some PROD_ID stuff fixed.
    -text note in sch for i2c jumper
    -voltage warning for > +5V RVR input damaging pi.
2019-03-29 post double check stuff - moved from PCA9306 to transistors
    -PCA level shifter is EOL, moved to transistor conversion.
    -added VCC range note in SCH
    -fixed a trace off of PCA PWM chip
    -PROD_ID fixes on LEDs
    -moved measure to show units
2019-04-05 Bumped the QWIIC label to 5mm package
    didn't print very cleanly at the 3mm size on the protos from jlcpcb, so bumped it up to 5mm package.
2019-04-16 Added 3.3V test point - gonna need this for properly testing the CH340
2019-04-16 cleaned up wire stubs
2019-04-26 Reverse current blocking diodes and more
    -Added reverse current blocking circuits.
    -Added auto switching isolation fet between Pi 5V rail and servo rail.
2019-04-29 schematic cleanup and some part positioning
2019-04-30 Placed all ideal diodes and routed most things
    still need a cap and test points placed and routed.
2019-05-01 V12 routed
2019-05-01 qwiic logo line width and some final minor tweaks
    nudged pi iso jumper away to avoid polarity mark on raspi gpio header.
    approved DRC errors.
    Updated to correct width qwiic logo to avoid long cam jobs
2019-05-02 Corrected package on OR gate
2019-05-03 Added tRestrict around standofs as required by HAT specs
    Also moved to correct 2.5 A PTC (1812 package).
2019-05-05 created python function for setting servo
    The original examples address each channel manually. I wanted a function I could call with channel and position for testing.
    While loop at bottom is good for testing each channel in sequence.
2019-05-05 final stuff during eng check for reds
    Schematic cleanup.
    Corrected OR Gate in latest library to correct SOT353 (was from older library)
    Added PROD_ID to dual PNP (TRAN-14386)
    moved some vias around to avoid cutting into silk.
    re-routed some "natural bridges" on bottom parts.
2019-05-06 qc double-check changes - and SS mods
    -bumped version to v20 (was previously v12)
    -Moved bottom parts for more clearance from SS route
2019-05-07 fixing DRC wire stubs, and clearance issues, ready for SS check
2019-05-07 fixed overlap issue with trans/mosfet neat servo header
    also lead to more clearance
2019-05-07 Fixed a couple leftover nasty traces, moved one more resistor up top for more clearance
2019-05-07 groupd design review changes
    -changes servo rail GND silk to G (there was a resistor sitting right on top of silk - derp)
    -nudges some vias for better ground flow.
    -removed polarity mark on dual pnp package
2019-05-07 fixed a non-critical "hidden" airwire within one of the huge traces.
2019-05-08 Changed name silk label to "Pi Servo pHAT" (buzzard)
2019-06-04 Fixed RX/TX on RVR 4-pin header
    -swapped rx/tx lines on the RVR header.
    -updated board buzzard labels on the header to reflect correction (and note, they are labeled in relation to the raspi)
    -bumped version to v21 in brd and sch
    -added RVR pin names in schematic next to 4-pin header. Put it on info layer. Just there to clarify what those pins are (in relation to the RVR).
    -moved test point (TP23) 0.05 inch east/right to gain more clarance from nearby bottom resistor (R13).
2019-06-06 final changes at group review
    -added test point to pi RXI
2019-06-06 Changing files names to match product name
2019-06-28 Updating resistor values for LEDs
    330 for green and 1K for yellow.
2019-07-11 Update: current product information
2019-07-12 Pi Servo pHAT Hookup Guide Examples
    Examples for hookup guide
